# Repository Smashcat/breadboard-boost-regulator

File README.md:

# Breadboard Boost Regulator

This is a small boost regulator circuit designed for use on a breadboard. It can be fully manufacturered at JLCPCB using the gerbers.zip BOM.csv and mount.csv files. The design here produces 12.5V from 3V to 9V input. It can switch around one amp, so the output current depends on the input voltage (e.g. at 9V input, it can produce 600mA current, but at 3V input, only around 70mA due to inefficiencies). The board has 2 outputs, both the same, as the minimum board size for PCBA from JLCPCB is 20mm x 20mm, plus I just wanted two outputs :) The schematic shows the formular to change the output voltage from the default. I used 2 resistors on one side of the divider to allow more flexibility when choosing parts. I have used "basic parts" from the JLC library where possible, to reduce cost. The cost for 20 boards is currently around £26 + shipping! Obviously the cost per board reduces as the quantity increases.

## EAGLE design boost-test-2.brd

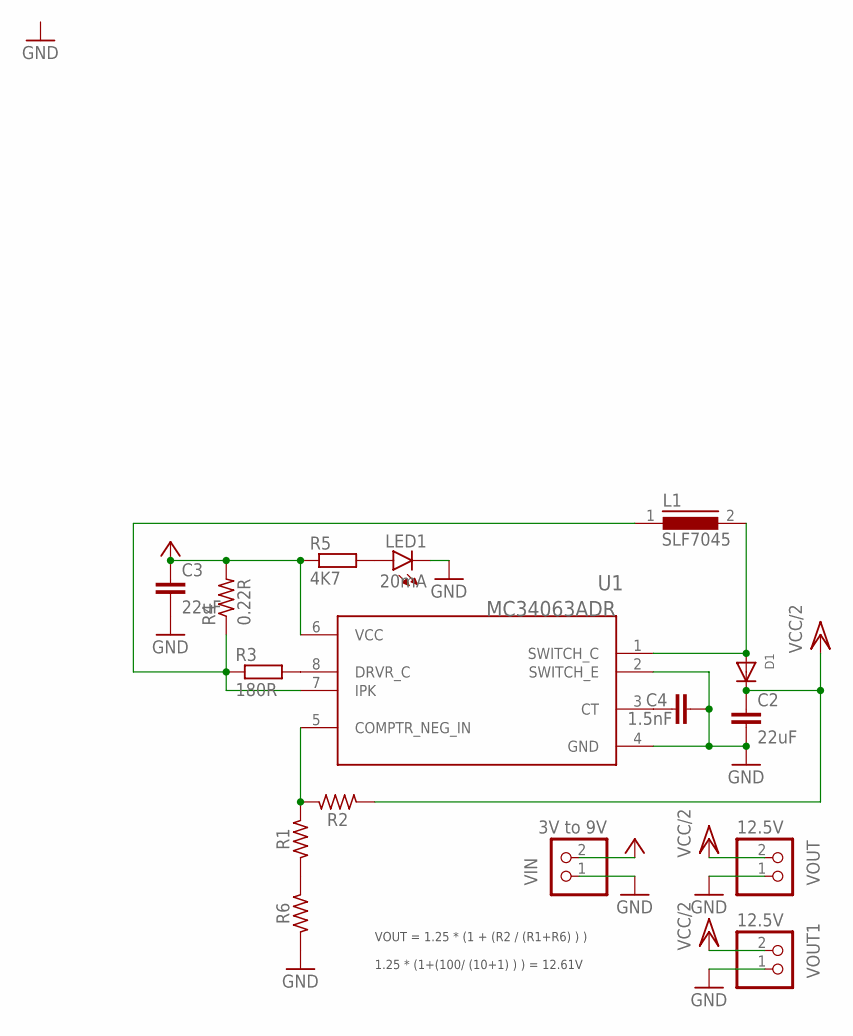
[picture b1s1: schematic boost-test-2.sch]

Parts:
C2, C3: 22uF; 0805
C4: 1.5nF; C0603
D1: ADAFRUIT_DIODESOD-123; ADAFRUIT_SOD-123
L1: SLF7045
LED1: 20mA; CHIP-LED0603
R1: 10K; 52101-101-REV-A_RC-MASTER-SMD_R0603MP
R2: 100K; 52101-101-REV-A_RC-MASTER-SMD_R0603MP
R3: 180R; R0402
R4: 0.22R; M0805
R5: 4K7; R0402
R6: 1K; 52101-101-REV-A_RC-MASTER-SMD_R0603MP
U1: MC34063ADR; SOIC127P599X175-8N
VIN: 3V to 9V; 1X02
VOUT, VOUT1: 12.5V; 1X02

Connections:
GND: C2.2, C3.2, C4.1, LED1.C, R6.1, U1.2 (SWITCH_E), U1.4 (GND), VIN.1, VOUT.1, VOUT1.1
unnamed: D1.A, L1.2, U1.1 (SWITCH_C)
unnamed: R3.2, U1.8 (DRVR_C)
unnamed: C4.2, U1.3 (CT)
unnamed: L1.1, R3.1, R4.1, U1.7 (IPK)
unnamed: R1.2, R2.2, U1.5 (COMPTR_NEG_IN)
unnamed: LED1.A, R5.2
unnamed: R1.1, R6.2
VCC: C3.1, R4.2, R5.1, U1.6 (VCC), VIN.2
VCC/2: C2.1, D1.C, R2.1, VOUT.2, VOUT1.2

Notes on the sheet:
VOUT = 1.25 * (1 + (R2 / (R1+R6) ) ) 1.25 * (1+(100/ (10+1) ) ) = 12.61V

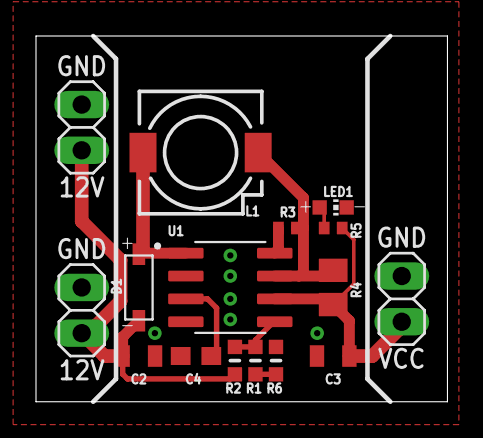
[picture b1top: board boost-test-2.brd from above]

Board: 2 copper layers, 22.9 x 20.3 mm, 16 parts (0 on the bottom side), 10 nets.

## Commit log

2021-05-14 Increased size of board.png
2021-05-14 Null
2021-05-14 Added datasheet for boost regulator IC

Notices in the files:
parts and their libraries:
SparkFun-Capacitors: Licensing: Creative Commons ShareAlike 4.0 International - https://creativecommons.org/licenses/by-sa/4.0
